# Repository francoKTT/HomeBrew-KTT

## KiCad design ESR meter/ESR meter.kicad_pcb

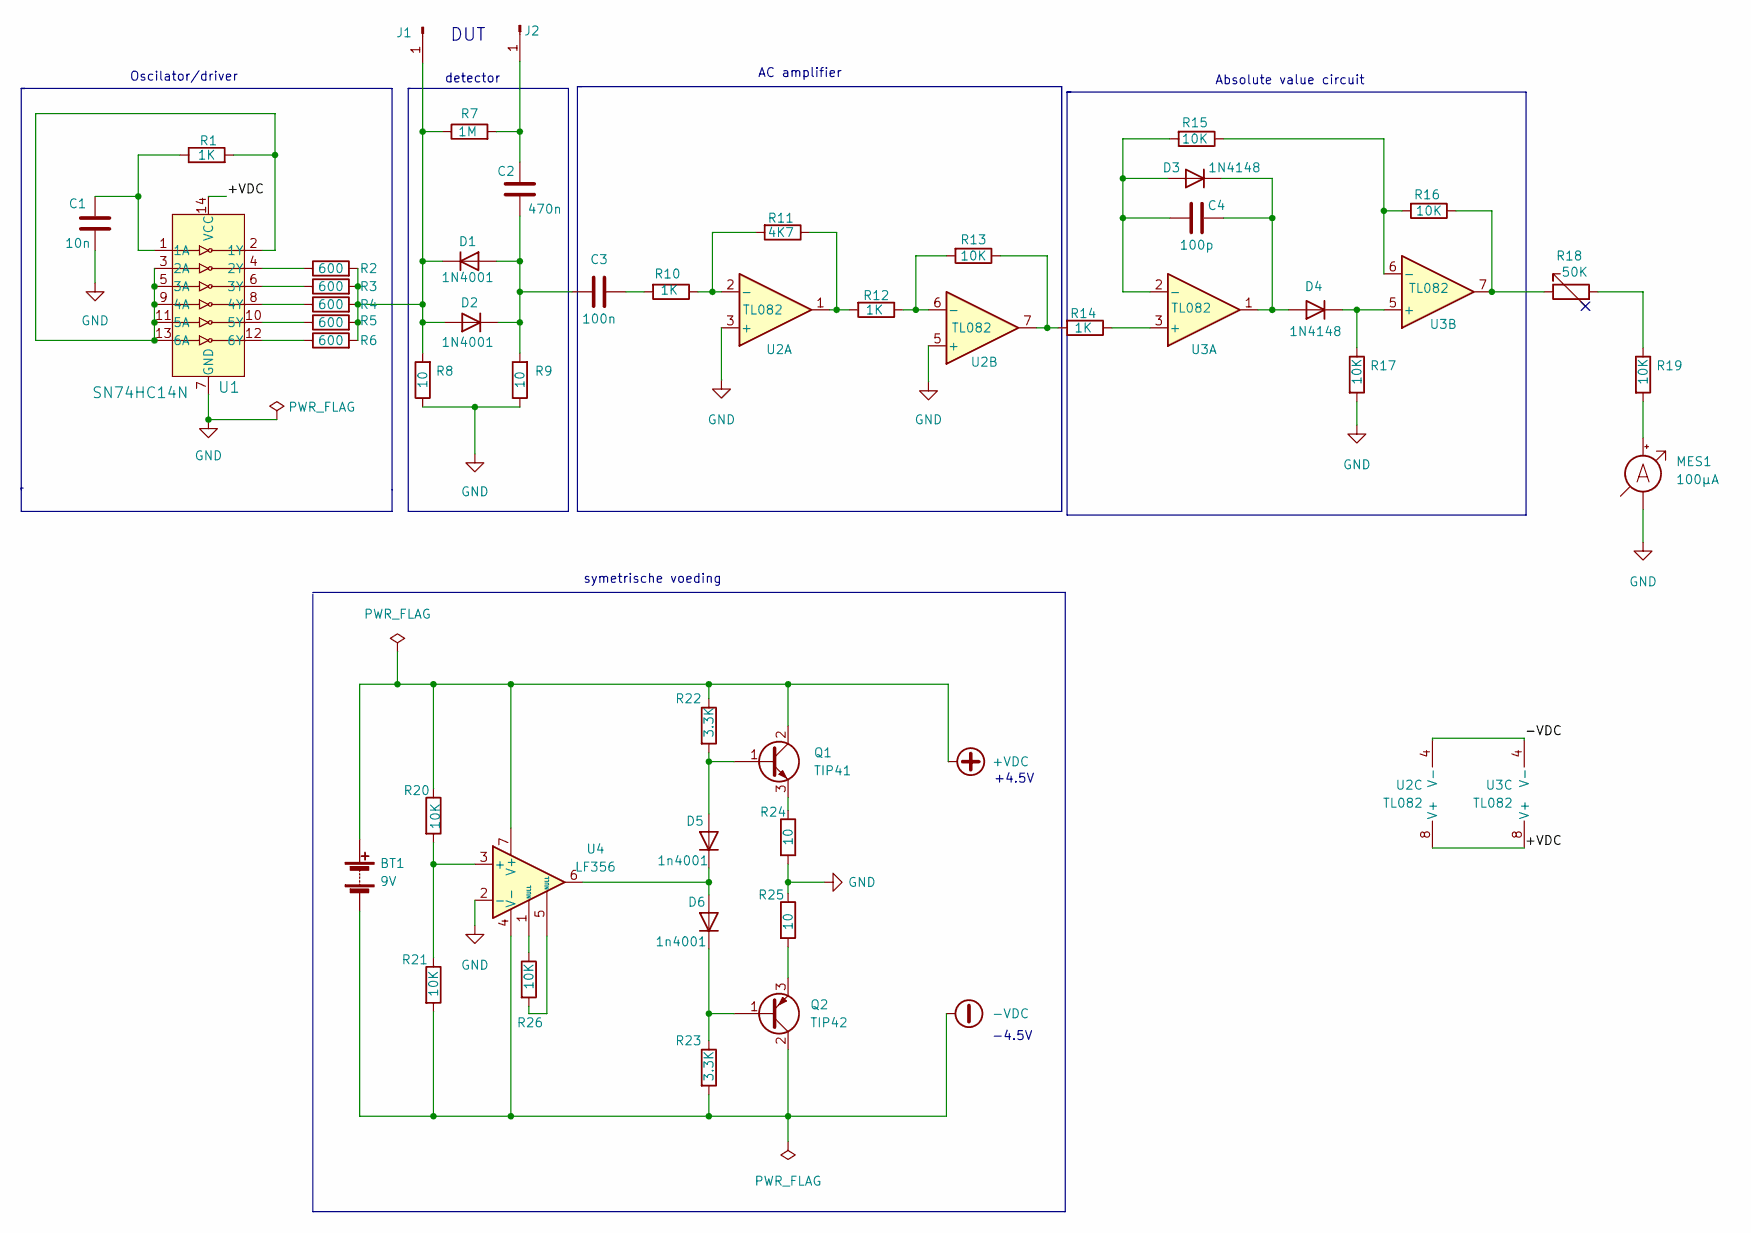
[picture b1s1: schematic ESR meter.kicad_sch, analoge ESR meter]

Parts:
BT1: 9V; PinHeader_1x02_P2.54mm_Vertical
C1: 10n; C_Disc_D4.3mm_W1.9mm_P5.00mm
C2: 470n; C_Disc_D4.3mm_W1.9mm_P5.00mm
C3: 100n; C_Disc_D4.3mm_W1.9mm_P5.00mm
C4: 100p; C_Disc_D4.3mm_W1.9mm_P5.00mm
D1, D2: 1N4001; D_DO-15_P10.16mm_Horizontal
D3, D4: 1N4148; D_DO-35_SOD27_P7.62mm_Horizontal
D5, D6: 1n4001; D_DO-15_P10.16mm_Horizontal
J1, J2: Conn_01x01_Male; PinHeader_1x01_P2.54mm_Vertical
MES1: 100µA; PinHeader_1x02_P2.54mm_Vertical
Q1: TIP41; TO-220-3_Vertical
Q2: TIP42; TO-220-3_Vertical
R1, R10, R12, R14: 1K; R_Axial_DIN0207_L6.3mm_D2.5mm_P10.16mm_Horizontal
R2, R3, R4, R5, R6: 600; R_Axial_DIN0207_L6.3mm_D2.5mm_P10.16mm_Horizontal
R7: 1M; R_Axial_DIN0207_L6.3mm_D2.5mm_P10.16mm_Horizontal
R8, R9, R24, R25: 10; R_Axial_DIN0207_L6.3mm_D2.5mm_P10.16mm_Horizontal
R11: 4K7; R_Axial_DIN0207_L6.3mm_D2.5mm_P10.16mm_Horizontal
R13, R15, R16, R17, R19, R20, R21, R26: 10K; R_Axial_DIN0207_L6.3mm_D2.5mm_P10.16mm_Horizontal
R18: 50K; Potentiometer_ACP_CA6-H2,5_Horizontal
R22, R23: 3.3K; R_Axial_DIN0207_L6.3mm_D2.5mm_P10.16mm_Horizontal
U1: SN74HC14N; DIP-14_W3mm; MPN SN74HC14N; Digi-Key_PN 296-1577-5-ND
U2, U3: TL082; DIP-8_W7.62mm
U4: LF356; DIP-8_W7.62mm

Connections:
+VDC: BT1.1 (+), Q1.2 (C), R20.1, R22.1, U1.14 (VCC), U2.8 (V+), U3.8 (V+), U4.7 (V+)
-VDC: BT1.2 (-), Q2.2 (C), R21.2, R23.2, U2.4 (V-), U3.4 (V-), U4.4 (V-)
GND: C1.2, MES1.1 (-), R8.1, R9.1, R17.2, R24.2, R25.1, U1.7 (GND), U2.3 (+), U2.5 (+), U4.2 (-)
unnamed: C1.1, R1.1, U1.1 (1A)
unnamed: C2.1, C3.1, D1.2 (A), D2.1 (K), R9.2
unnamed: C2.2, J2.1, R7.2
unnamed: C3.2, R10.2
unnamed: C4.1, D3.2 (A), R15.2, U3.2 (-)
unnamed: C4.2, D3.1 (K), D4.2 (A), U3.1
unnamed: D1.1 (K), D2.2 (A), J1.1, R2.2, R3.2, R4.2, R5.2, R6.2, R7.1, R8.2
unnamed: D4.1 (K), R17.1, U3.5 (+)
unnamed: D5.1 (K), D6.2 (A), U4.6
unnamed: D5.2 (A), Q1.1 (B), R22.2
unnamed: D6.1 (K), Q2.1 (B), R23.1
unnamed: MES1.2 (+), R19.2
unnamed: Q1.3 (E), R24.1
unnamed: Q2.3 (E), R25.2
unnamed: R1.2, U1.2 (1Y), U1.3 (2A), U1.5 (3A), U1.9 (4A), U1.11 (5A), U1.13 (6A)
unnamed: R2.1, U1.4 (2Y)
unnamed: R3.1, U1.6 (3Y)
unnamed: R4.1, U1.8 (4Y)
unnamed: R5.1, U1.10 (5Y)
unnamed: R6.1, U1.12 (6Y)
unnamed: R10.1, R11.2, U2.2 (-)
unnamed: R11.1, R12.2, U2.1
unnamed: R12.1, R13.2, U2.6 (-)
unnamed: R13.1, R14.2, U2.7
unnamed: R14.1, U3.3 (+)
unnamed: R15.1, R16.2, U3.6 (-)
unnamed: R16.1, R18.1, U3.7
unnamed: R18.2, R19.1
unnamed: R20.2, R21.1, U4.3 (+)
unnamed: R26.1, U4.1 (NULL)
unnamed: R26.2, U4.5 (NULL)

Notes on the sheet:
AC amplifier
DUT
+4.5V
Oscilator/driver
symetrische voeding
Absolute value circuit
detector
-4.5V

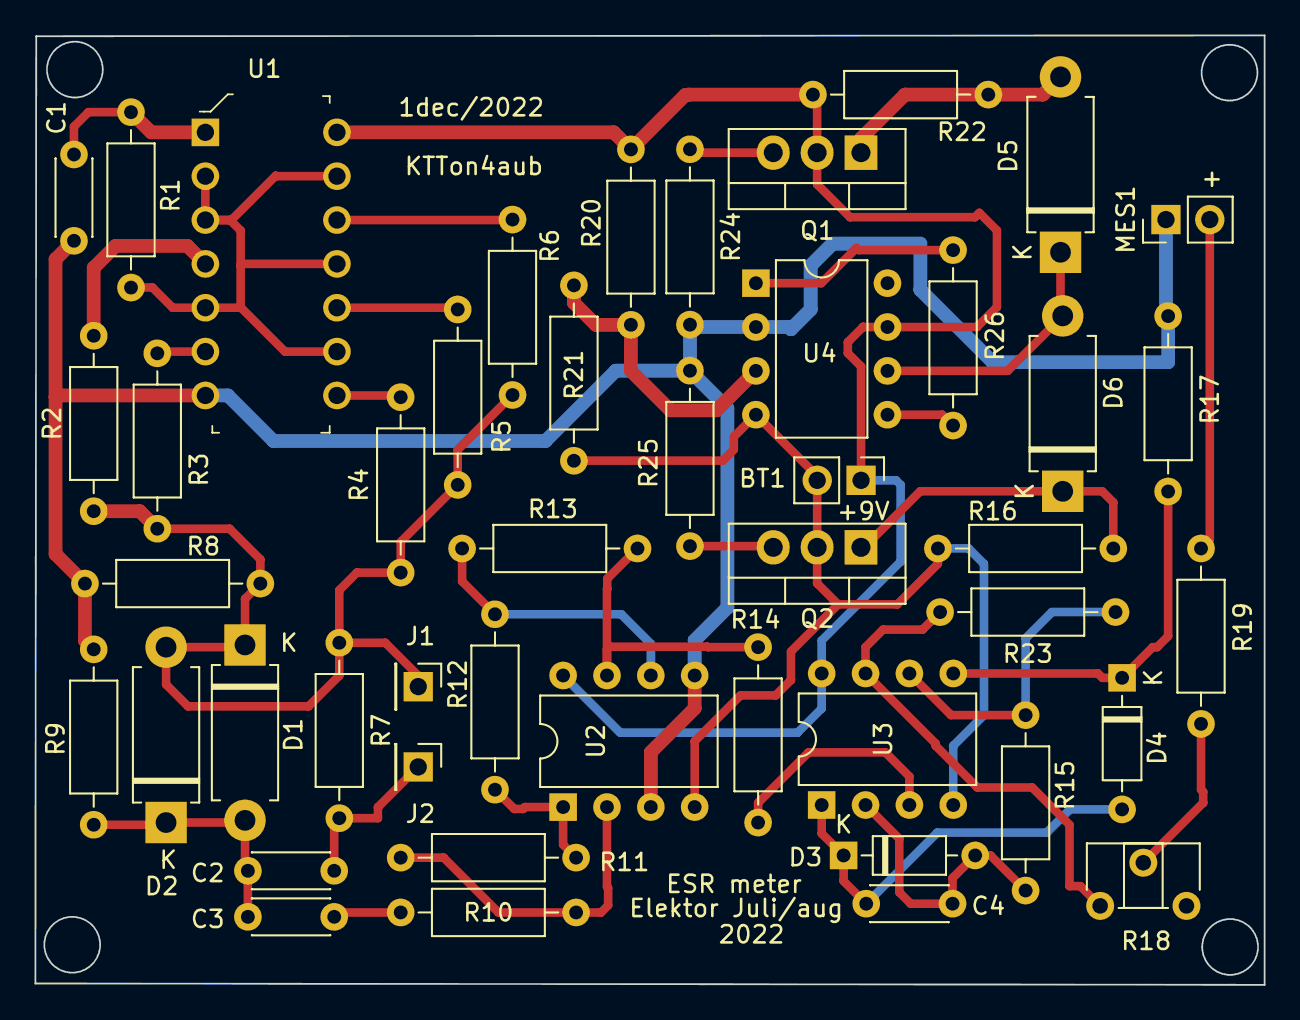
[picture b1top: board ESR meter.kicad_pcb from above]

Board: 2 copper layers, 71.2 x 55.0 mm, 46 parts (0 on the bottom side), 34 nets.

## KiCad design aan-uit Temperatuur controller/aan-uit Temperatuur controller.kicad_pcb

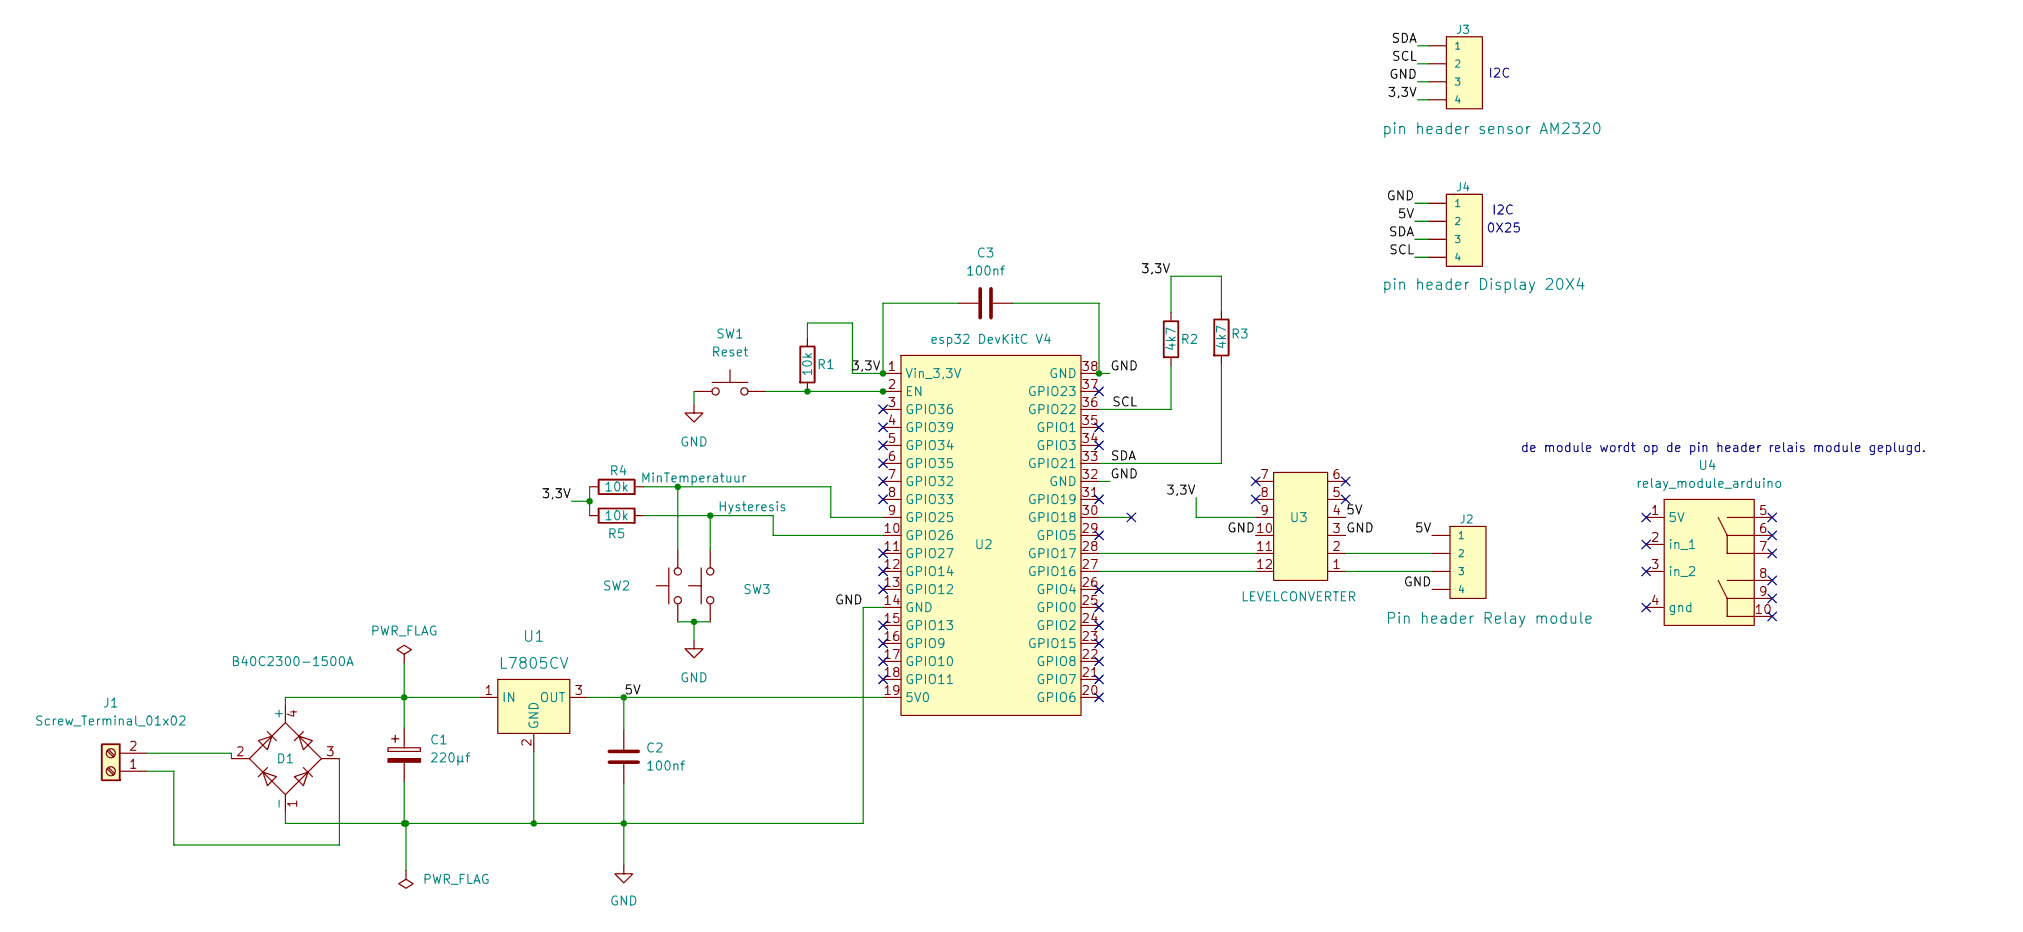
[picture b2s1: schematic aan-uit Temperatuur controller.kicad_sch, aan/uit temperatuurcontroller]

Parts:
C1: 220µf; CP_Radial_D6.3mm_P2.50mm
C2, C3: 100nf; C_Rect_L7.0mm_W3.5mm_P2.50mm_P5.00mm
D1: B40C2300-1500A; Diode_Bridge_19.0x3.5x10.0mm_P5.0mm
J1: Screw_Terminal_01x02; THERM-BLOCK-1x2_P5.08mm_frvdb
J2: CONN_04; 2_relay_shield_frvdb
J3, J4: CONN_04; PinHeader_1x04_P2.54mm_Vertical
R1, R4, R5: 10k; R_Axial_DIN0414_L11.9mm_D4.5mm_P15.24mm_Horizontal
R2, R3: 4k7; R_Axial_DIN0414_L11.9mm_D4.5mm_P15.24mm_Horizontal
SW1: Reset; SW_PUSH_6mm
SW2: MinTemperatuur; SW_PUSH_6mm
SW3: Hysteresis; SW_PUSH_6mm
U1: L7805CV; TO-220-3_Horizontal_TabDown; MPN L7805CV; Digi-Key_PN 497-1443-5-ND
U2: esp32 DevKitC V4; esp32devkitC38_dil_on4aub
U3: LEVELCONVERTER; frvdb_DIP-12_W10.16_socket
U4: relay_module_arduino

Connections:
/3,3V: C3.1, J3.4, R1.1, R2.1, R3.1, R4.1, R5.1, U2.1 (Vin_3,3V), U3.9
/5V: C2.1, J2.1, J4.2, U1.3 (OUT), U2.19 (5V0), U3.4
/SCL: J3.2, J4.4, R2.2, U2.36 (GPIO22)
/SDA: J3.1, J4.3, R3.2, U2.33 (GPIO21)
GND: C1.2, C2.2, C3.2, D1.1 (-), J2.4, J3.3, J4.1, SW1.1, SW2.1, SW3.1, U1.2 (GND), U2.14 (GND), U2.32 (GND), U2.38 (GND), U3.3, U3.10
unnamed: C1.1, D1.4 (+), U1.1 (IN)
unnamed 6: D1.2, J1.2; also elsewhere on the board
unnamed 7: D1.3, J1.1; also elsewhere on the board
unnamed: J2.2, U3.2
unnamed: J2.3, U3.1
unnamed: R1.2, SW1.2, U2.2 (EN)
unnamed: R4.2, SW2.2, U2.9 (GPIO25)
unnamed: R5.2, SW3.2, U2.10 (GPIO26)
unnamed: U2.27 (GPIO16), U3.12
unnamed: U2.28 (GPIO17), U3.11

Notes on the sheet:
I2C
0X25
de module wordt op de pin header relais module geplugd.

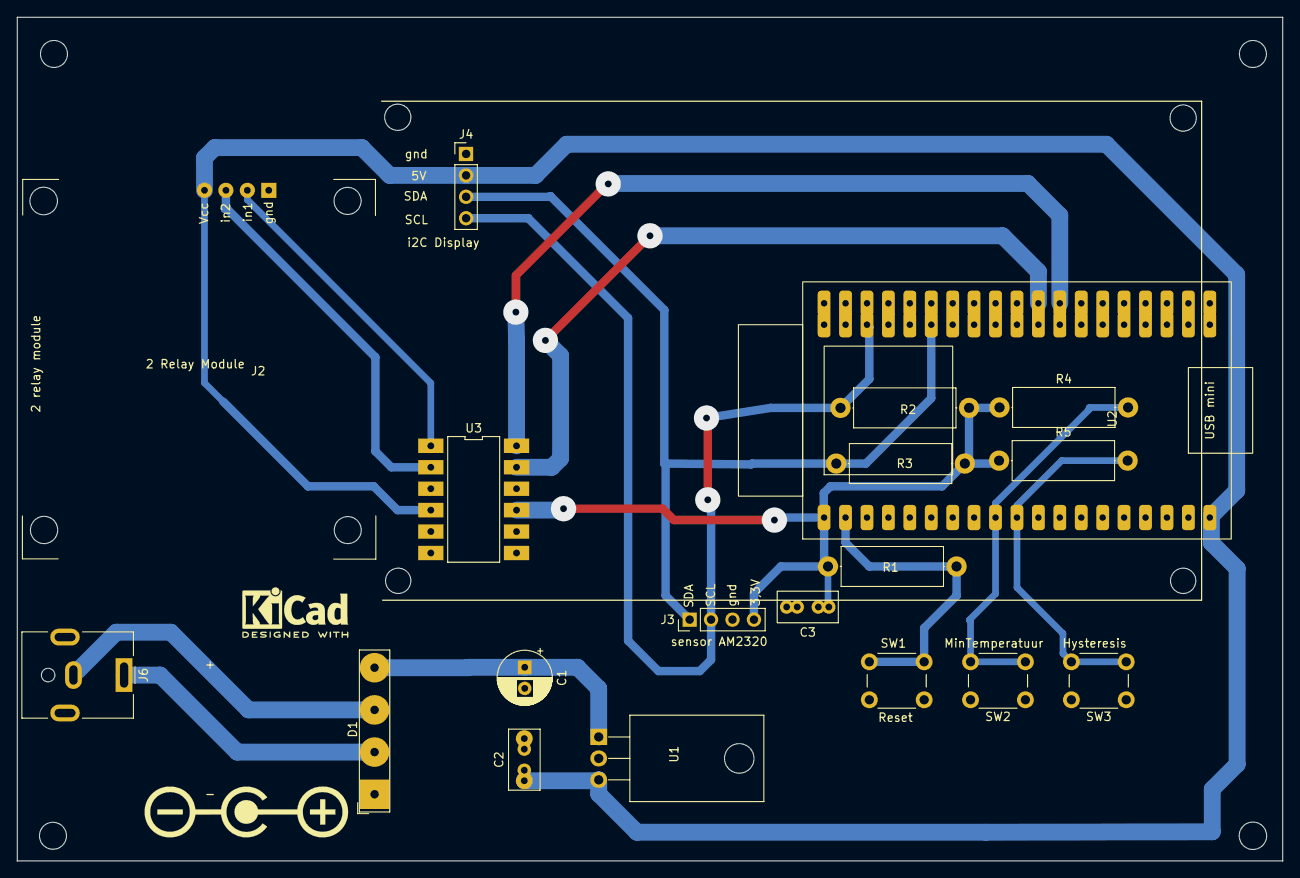
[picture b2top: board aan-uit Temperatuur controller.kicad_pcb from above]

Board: 2 copper layers, 150.0 x 100.0 mm, 19 parts (0 on the bottom side), 15 nets.

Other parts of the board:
J6: Barrel_Jack_Switch; BarrelJack_CUI_PJ-063AH_Horizontal

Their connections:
unnamed 6: J6.1; also elsewhere on the board
unnamed 7: J6.2; also elsewhere on the board

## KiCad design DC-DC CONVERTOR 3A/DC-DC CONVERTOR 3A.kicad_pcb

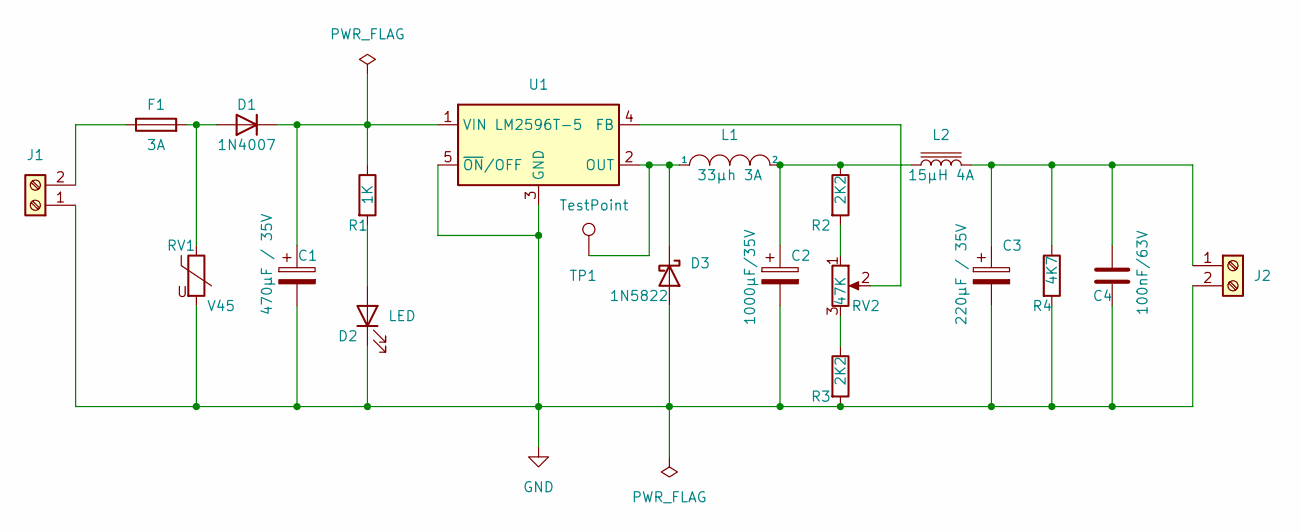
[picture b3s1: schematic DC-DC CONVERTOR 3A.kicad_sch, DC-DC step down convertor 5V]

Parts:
C1: 470µF / 35V; CP_Radial_D16.0mm_P7.50mm
C2: 1000µF/35V; CP_Radial_D18.0mm_P7.50mm
C3: 220µF / 35V; CP_Radial_D12.5mm_P5.00mm
C4: 100nF/63V; C_Disc_D4.3mm_W1.9mm_P5.00mm
D1: 1N4007; D_DO-41_SOD81_P10.16mm_Horizontal
D2: LED; LED_D3.0mm
D3: 1N5822; D_DO-201AD_P15.24mm_Horizontal
F1: 3A; Fuseholder_Clip-5x20mm_Keystone_3517_Inline_P23.11x6.76mm_D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
J1, J2: Screw_Terminal_01x02; TerminalBlock_Phoenix_MKDS-1,5-2-5.08_1x02_P5.08mm_Horizont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
L1: 33µh 3A; L_Radial_D12.5mm_P7.00mm_Fastron_09HCP
L2: 15µH 4A; L_Radial_D12.5mm_P7.00mm_Fastron_09HCP
R1: 1K; R_Axial_DIN0207_L6.3mm_D2.5mm_P10.16mm_Horizontal
R2, R3: 2K2; R_Axial_DIN0207_L6.3mm_D2.5mm_P10.16mm_Horizontal
R4: 4K7; R_Axial_DIN0207_L6.3mm_D2.5mm_P10.16mm_Horizontal
RV1: V45; R_Axial_DIN0207_L6.3mm_D2.5mm_P10.16mm_Horizontal
RV2: 47K; Potentiometer_Bourns_3266Y_Vertical
TP1: TestPoint; TestPoint_2Pads_Pitch2.54mm_Drill0.8mm
U1: LM2596T-5; TO-220-5_P3.4x3.8mm_StaggerOdd_Lead7.13mm_TabDown

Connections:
GND: C1.2, C2.2, C3.2, C4.2, D2.1 (K), D3.2 (A), J1.1, J2.2, R3.2, R4.2, RV1.2, U1.3 (GND), U1.5 (~ON/OFF)
unnamed: C1.1, D1.1 (K), R1.1, U1.1 (VIN)
unnamed: C2.1, L1.2, L2.1, R2.1
unnamed: C3.1, C4.1, J2.1, L2.2, R4.1
unnamed: D1.2 (A), F1.2, RV1.1
unnamed: D2.2 (A), R1.2
unnamed: D3.1 (K), L1.1, TP1.1, U1.2 (OUT)
unnamed: F1.1, J1.2
unnamed: R2.2, RV2.1
unnamed: R3.1, RV2.3
unnamed: RV2.2, U1.4 (FB)

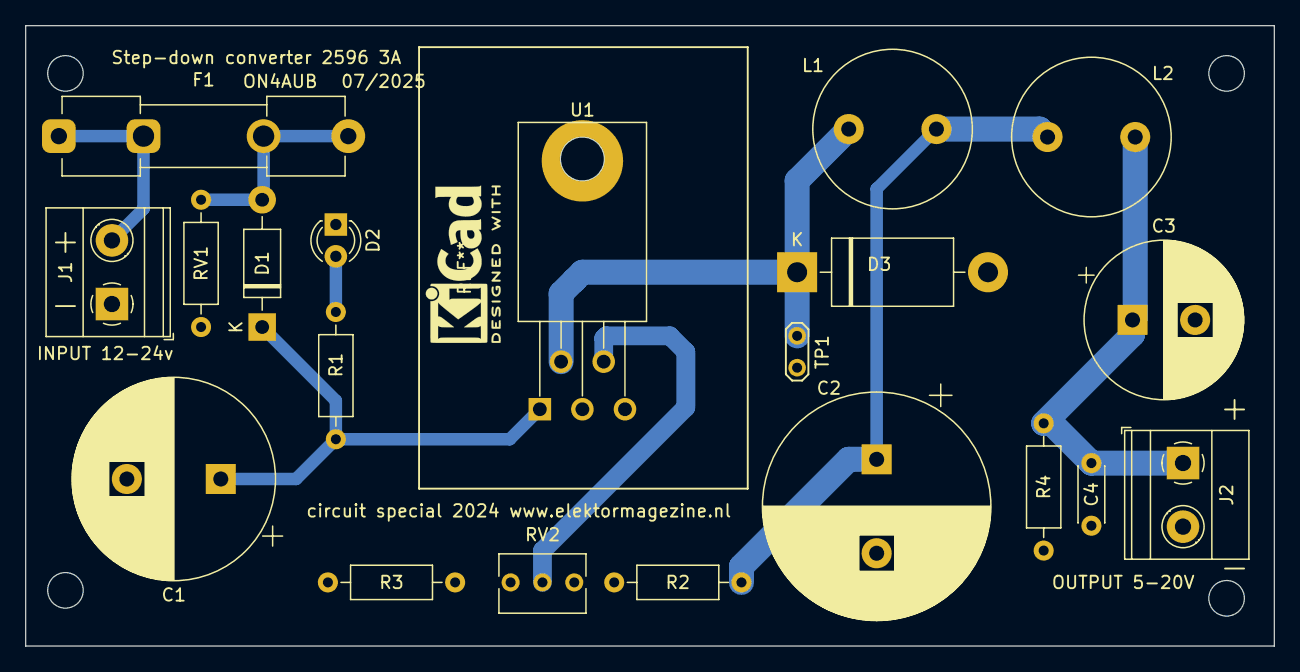
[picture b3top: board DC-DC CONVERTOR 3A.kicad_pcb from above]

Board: 2 copper layers, 99.7 x 49.5 mm, 20 parts (0 on the bottom side), 11 nets.

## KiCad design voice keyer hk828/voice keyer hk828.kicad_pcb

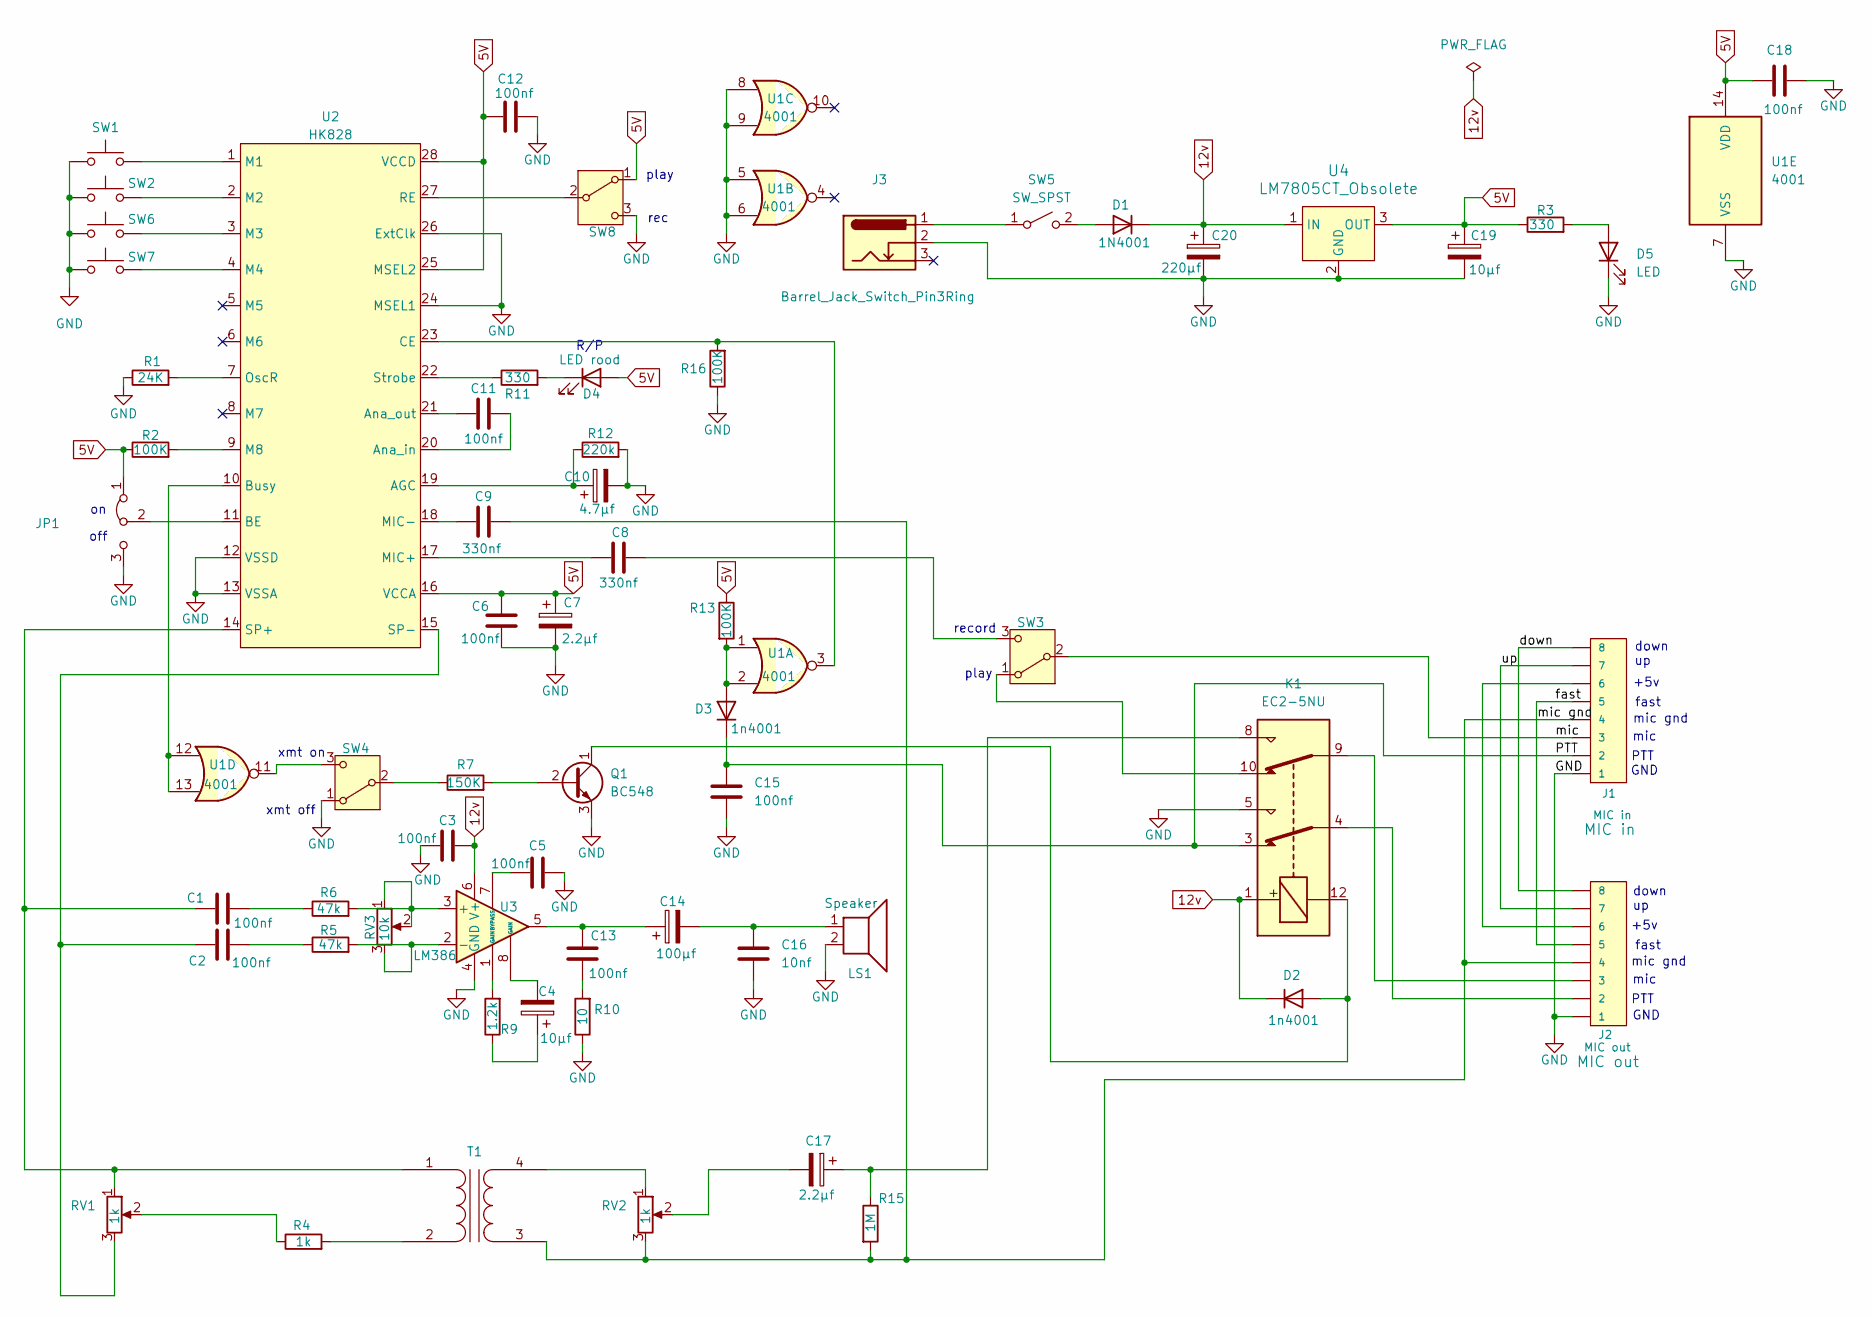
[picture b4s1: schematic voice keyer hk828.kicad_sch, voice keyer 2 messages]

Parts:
C1, C2, C3, C5, C6, C11, C12, C13, C15, C18: 100nf; C_Disc_D5.0mm_W2.5mm_P5.00mm
C4, C19: 10µf; CP_Radial_D5.0mm_P2.50mm
C7, C17: 2.2µf; CP_Radial_D5.0mm_P2.50mm
C8, C9: 330nf; C_Disc_D5.0mm_W2.5mm_P5.00mm
C10: 4.7µf; CP_Radial_D5.0mm_P2.50mm
C14: 100µf; CP_Radial_D5.0mm_P2.50mm
C16: 10nf; C_Disc_D5.0mm_W2.5mm_P5.00mm
C20: 220µf; CP_Radial_D10.0mm_P3.50mm
D1: 1N4001; D_DO-41_SOD81_P10.16mm_Horizontal
D2, D3: 1n4001; D_DO-41_SOD81_P10.16mm_Horizontal
D4: LED rood; LED_D3.0mm
D5: LED; LED_D3.0mm
J1: MIC in; PinHeader_1x08_P2.54mm_Vertical
J2: MIC out; PinHeader_1x08_P2.54mm_Vertical
J3: Barrel_Jack_Switch_Pin3Ring; BarrelJack_GCT_DCJ200-10-A_Horizontal
JP1: Jumper_3_Bridged12; PinHeader_1x03_P2.54mm_Vertical
K1: EC2-5NU; Relay_DPDT_Kemet_EC2_NU
LS1: Speaker; jumper_2pin_2.54mm_frvdb
Q1: BC548; TO-92_Inline
R1: 24K; R_Axial_DIN0207_L6.3mm_D2.5mm_P5.08mm_Vertical
R2, R13, R16: 100K; R_Axial_DIN0207_L6.3mm_D2.5mm_P5.08mm_Vertical
R3, R11: 330; R_Axial_DIN0207_L6.3mm_D2.5mm_P5.08mm_Vertical
R4: 1k; R_Axial_DIN0207_L6.3mm_D2.5mm_P5.08mm_Vertical
R5, R6: 47k; R_Axial_DIN0207_L6.3mm_D2.5mm_P5.08mm_Vertical
R7: 150K; R_Axial_DIN0207_L6.3mm_D2.5mm_P5.08mm_Vertical
R9: 1.2k; R_Axial_DIN0207_L6.3mm_D2.5mm_P5.08mm_Vertical
R10: 10; R_Axial_DIN0207_L6.3mm_D2.5mm_P5.08mm_Vertical
R12: 220k; R_Axial_DIN0207_L6.3mm_D2.5mm_P5.08mm_Vertical
R15: 1M; R_Axial_DIN0207_L6.3mm_D2.5mm_P5.08mm_Vertical
RV1, RV2: 1k; Potentiometer_Bourns_3296W_Vertical
RV3: 10k; PinHeader_1x03_P2.54mm_Vertical
SW1, SW2, SW6, SW7: SW_Push; jumper_2pin_2.54mm_frvdb
SW3, SW4, SW8: SW_SPDT; PinHeader_1x03_P2.54mm_Vertical
SW5: SW_SPST; PinHeader_1x02_P2.54mm_Vertical
T1: Transformer_1P_1S; Transformer_NF_ETAL_1-1_P1200
U1: 4001; CERDIP-14_W7.62mm_SideBrazed_LongPads
U2: HK828; DIP-28_W15.24mm_LongPads
U3: LM386; CERDIP-8_W7.62mm_SideBrazed_LongPads
U4: LM7805CT_Obsolete; TO-220-3_Vertical; MPN LM7805CT; Digi-Key_PN LM7805CT-ND

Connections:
5V: C6.2, C7.1, C12.1, C18.1, C19.1, D4.2 (A), JP1.1 (A), R2.1, R3.1, R13.1, SW8.1 (A), U1.14 (VDD), U2.16 (VCCA), U2.25 (MSEL2), U2.28 (VCCD), U4.3 (OUT)
12v: C3.2, C20.1, D1.1 (K), D2.1 (K), K1.1, U3.6 (V+), U4.1 (IN)
/PTT: C15.1, D3.1 (K), J1.2, K1.3
/down: J1.8, J2.8
/mic: J1.3, SW3.2 (B)
/up: J1.7, J2.7
GND: C3.1, C5.2, C6.1, C7.2, C10.2, C12.2, C15.2, C16.2, C18.2, C19.2, C20.2, D5.1 (K), J1.1, J2.1, J3.2, JP1.3 (B), K1.5, LS1.2, Q1.3 (E), R1.1, R10.1, R12.2, R16.1, SW1.1, SW2.1, SW4.1 (A), SW6.1, SW7.1, SW8.3 (C), U1.5, U1.6, U1.7 (VSS), U1.8, U1.9, U2.12 (VSSD), U2.13 (VSSA), U2.24 (MSEL1), U2.26 (ExtClk), U3.4 (GND), U4.2 (GND)
unnamed: C1.2, R6.1
unnamed: C2.2, R5.1
unnamed: C4.1, R9.1
unnamed: C4.2, U3.8 (GAIN)
unnamed: C13.1, C14.1, U3.5
unnamed: C13.2, R10.2
unnamed: C14.2, C16.1, LS1.1
unnamed: C17.1, K1.8, R15.1
unnamed: C17.2, RV2.2
unnamed: D1.2 (A), SW5.2 (B)
unnamed: D2.2 (A), K1.12, Q1.1 (C)
unnamed: D3.2 (A), R13.2, U1.1, U1.2
unnamed: D4.1 (K), R11.2
unnamed: D5.2 (A), R3.2
unnamed: J1.6, J2.6
unnamed: J2.2, K1.4
unnamed: J2.3, K1.9
unnamed: JP1.2 (C), U2.11 (BE)
unnamed: Q1.2 (B), R7.2
unnamed: R4.1, RV1.2
unnamed: R9.2, U3.1 (GAIN)
unnamed: K1.10, SW3.1 (A)
unnamed: C8.1, SW3.3 (C)
unnamed: R7.1, SW4.2 (B)
unnamed: SW4.3 (C), U1.11
unnamed: J3.1, SW5.1 (A)
unnamed: SW8.2 (B), U2.27 (RE)
unnamed: C1.1, RV1.1, T1.1 (AA), U2.14 (SP+)
unnamed: R4.2, T1.2 (AB)
unnamed: RV2.1, T1.4 (SB)
unnamed: C10.1, R12.1, U2.19 (AGC)
unnamed: C11.2, U2.20 (Ana_in)
unnamed: C11.1, U2.21 (Ana_out)
unnamed: U1.12, U1.13, U2.10 (Busy)
unnamed: R16.2, U1.3, U2.23 (CE)
unnamed: SW1.2, U2.1 (M1)
unnamed: SW2.2, U2.2 (M2)
unnamed: SW6.2, U2.3 (M3)
unnamed: SW7.2, U2.4 (M4)
unnamed: R2.2, U2.9 (M8)
unnamed: C8.2, U2.17 (MIC+)
unnamed: C9.1, U2.18 (MIC-)
unnamed: R1.2, U2.7 (OscR)
unnamed: C2.1, RV1.3, U2.15 (SP-)
unnamed: R11.1, U2.22 (Strobe)
unnamed: R6.2, RV3.1, RV3.2, U3.3 (+)
unnamed: R5.2, RV3.3, U3.2 (-)
unnamed: C5.1, U3.7 (BYPASS)

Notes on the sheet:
down
mic gnd
+5v
mic
record
GND
R/P
play
off
xmt off
PTT
fast
xmt on
rec

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
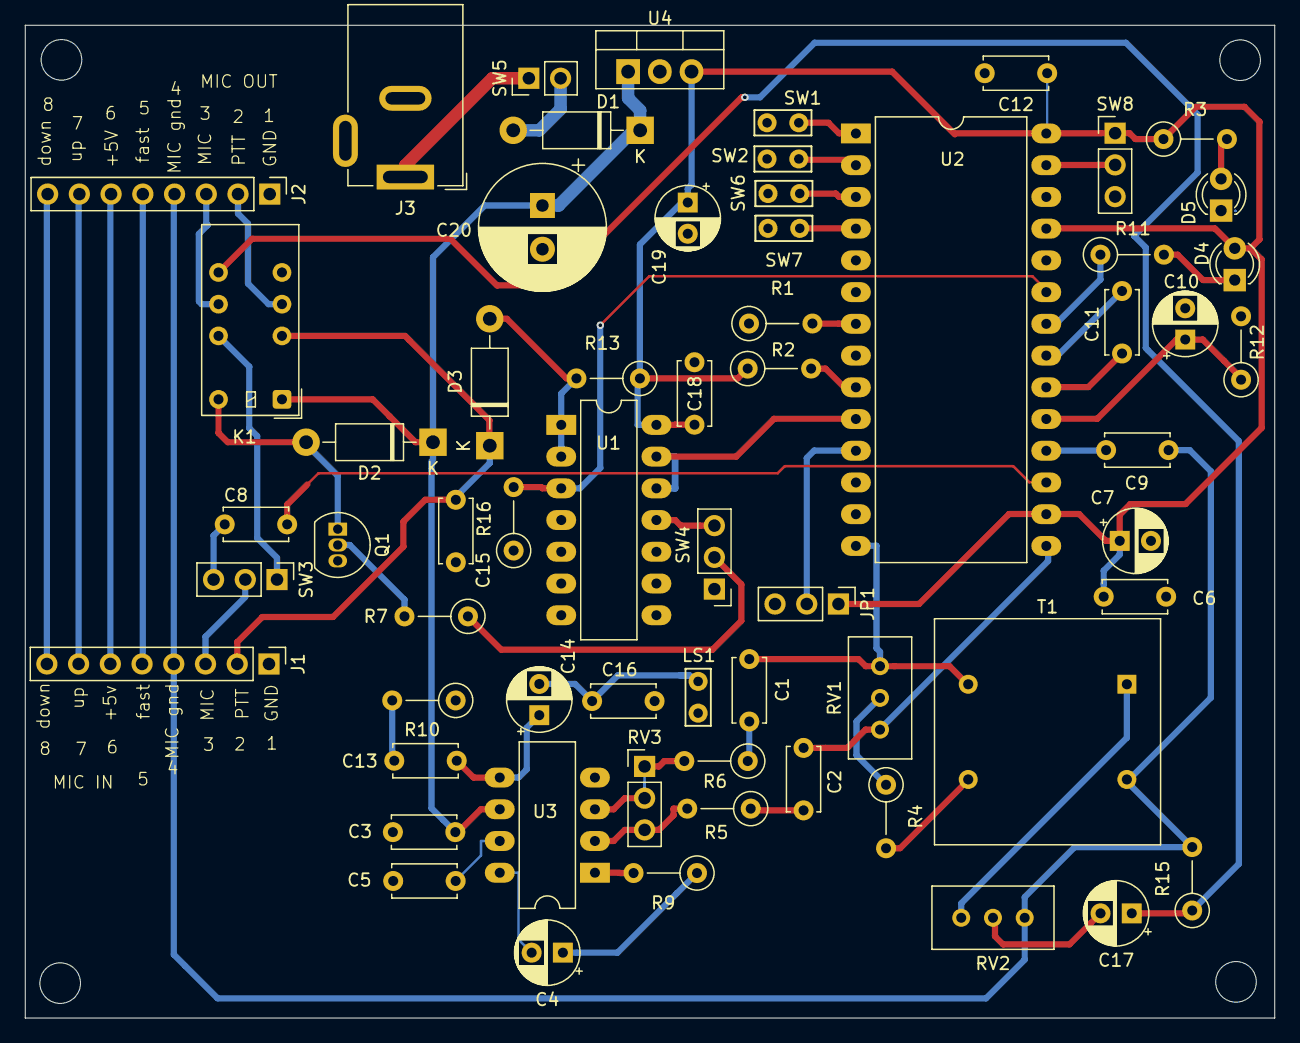
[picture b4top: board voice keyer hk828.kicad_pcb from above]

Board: 2 copper layers, 100.0 x 79.5 mm, 62 parts (0 on the bottom side), 57 nets.
